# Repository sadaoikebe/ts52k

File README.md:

# TS52K — 無線版

親指シフト（NICOLA配列）を前提に設計した、52キーの自作キーボードです。このブランチは、MDBT50Q-1MV2 と ZMK で動かす無線版です。ケースとプレートは RP2040 版と共通です。

解説記事: [親指シフトキーボードを作った話](https://qiita.com/sadaoikebe/items/e3715383058286457a23)

## 特徴

- **親指シフト専用設計** — かな入力だけでなく、英数レイヤーも親指シフトで打てる配列
- **52キー + ロータリーエンコーダ** — 50%サイズに親指キーを確保したレイアウト
- **ZMK** — 有線のときは USB HID、ケーブルを抜くと BLE
- **MDBT50Q-1MV2** — Raytac の nRF52840 モジュール。チップアンテナ付き。技適あり
- **USB-C が一つ** — 有線キーボード、充電、あとからの UF2
- **保護付きの LiPo** — 過放電保護はセル側。基板側コネクタはJST PH横挿しSMT、電池製品は後で選ぶ
- **JLCPCB で発注できる基板** — モジュールは在庫 0 なので、事前発注してから PCBA
- **FDM 3Dプリンタで出力できるケース** — 特殊な設備なしで製作可能

---

## このブランチ

回路図は無線版へ更新しました。既存の配置を引き継いだ親シートと、MDBT50Q・電源容量・LF水晶の子シートの2枚です。[回路図PDF](pcb/schematic-review/ts52k-wireless.pdf)と[配置元・確認記録](notes/wireless-schematic-layout.md)を参照してください。PCBは2026-11-10にU5を西端へ移し、GPIO割当てと西側の配置・配線を更新しました。[配置画像・記録](pcb/placement-review/README.md)を参照してください。取り込み判断・実機検証・無線版の製造データ作成は未了です。

現行の決定は[無線版の決定事項](notes/wireless-decisions.md)に集約しています。BOMは20品種・82点で（2026-11-11に電池の逆接続保護Q1を追加）、回路図から参照番号付きで照合済みです。ERCはエラー・警告とも0件。電池・ケース、SWD機材の購入判断は後日です。

使用しているKiCad MCPとローカル開発環境は[KiCad開発環境の記録](pcb/DEVELOPMENT.md)を参照してください。

## リポジトリ構成

```
pcb/     KiCad 10 プロジェクト。回路図・PCBは無線版、U5西端移設後
         子シート pcb/mdbt50q.kicad_sch
         schematic-review/ — PDF、画像、ERC、参照番号付きBOMと検査結果
         placement-review/ — PCB配置・配線画像と各時点の照合結果
         PLACEMENT.md — RP2040 版の基板レイアウトガイド
case/    FreeCAD ソース、3Dプリント用 3MF、プレート加工用 DXF
```

`pcb/` は無線版で使うシンボルとフットプリントを同梱しています。回路図とPCBの旧部品・旧ライブラリ参照は除去済みです。

| ライブラリ | 内容 |
| :--- | :--- |
| `MX_Only.pretty` | Cherry MX キースイッチのフットプリント（1U〜3U、7種） |
| `ts52k.kicad_sym` / `.pretty` | 無線版の選定済み20品種とMXシンボル。採用ランド15種を同梱 |
| `tag-connect.kicad_sym` | Tag-Connect TC2030のSWDシンボル。既定ランドは`ts52k.pretty`に同梱 |

選定済み部品の登録、回路図への反映とPCBへの取り込みは完了しています。[ライブラリの出典・変更・削除内容](pcb/LIBRARIES.md)と[部品ごとのシンボル／ランド対応表](pcb/wireless-library.csv)を参照してください。全配線を接続した後の設計レビュー・実機検証は残っています。

---

## 回路の構成

```
USB-C (J1) ─┬─ VBUS ─┬─→ BQ24072 IN（1 µF）
            │        └─ 2.2 Ω ─→ モジュール VBUS（パッド 32、4.7 µF）
            └─ D−/D+ ──→ モジュール パッド 34 / 35
                         ESD は H5VU10U。データ線に直列抵抗は置かない

BQ24072 OUT（4.7 µF）──→ モジュール VDDH（パッド 30）
BQ24072 BAT（4.7 µF）──→ JST PH 2極（1=BAT+、2=GND）──→ 保護付きセル

モジュール VDD（パッド 28）──→ J2 の 1 番。電圧は REGOUT0 = 3.3 V
モジュール ── 16本 ──→ キーマトリクス（6列×10行）
          ── 2本   ──→ エンコーダの回転（A=P1.11、B=P1.13）
          ── SWD ──→ J2 の 2 番 SWDIO（パッド 51）、4 番 SWCLK（パッド 53）
SW1 ──→ P0.18（nRESET）を GND へ。電源を切らずに 500 ms 以内の 2 回押しで UF2
```

モジュールは MDBT50Q-1MV2 です。P1MV2 との差はアンテナだけで、技適は両方にあります。外形は 10.5 × 15.5 × 2.05 mm、供給は 1.7〜5.5 V です。アンテナは削ったり、足したりしません。32 MHz と無線側のインダクタはモジュールの中にあります。GPIO は 48 本が 61 パッドに出ています。

### USB

J1 は HRO TYPE-C-31-M-12 のままです。CC1 / CC2 は 5.1 kΩ で GND、シールドは GND、D− / D+ / VBUS の ESD は H5VU10U です。D+ / D− の直列抵抗は、nRF の USB PHY に入っているので置きません。

PC に挿すと、ZMK は既定で USB HID に出します。ケーブルを抜くと最後の BLE プロファイルに戻ります。切り替えは `&out` で、選択は残ります。充電器のように HID を受け取らない相手では `OUT_BLE` にします。キーマップだけの変更は ZMK Studio が USB でも BLE でもできます。

VBUS（パッド 32）は、モジュールの USB 用 3.3 V レギュレータへの 5 V 入力です。充電 IC の出力はここへ入れません。

モジュールVBUS枝には、Nordic推奨・Raytac参考回路の2.2 Ωを入れます。C22939（0603・Basic）を1個、4.7 µFは抵抗の後、VBUSのESDは手前です。BQ24072 INは抵抗の手前から分岐します。[選定根拠と接続](notes/wireless-power-input.md)を参照してください。

### 電源

セルの電圧を VDDH（パッド 30）へ入れ、モジュール内のレギュレータでコアを作ります。ZMK の nice!nano v2 は `zmk,battery-nrf-vddh` で、このピンを読みます。外の 3.3 V で VDD と VDDH を短絡する結線にはしません。この基板には灯が無く、他の基板へ 3.3 V を出すピンもありません。

GPIO の High は REGOUT0 です。nice!nano のブートローダに合わせて 3.3 V にします。UICR の生の数値は、ブートローダのソースからは写していません。未設定のままでは VDD が 1.8 V になります。

検証済みのZMK main最小構成に合わせ、REG0（高電圧側）・REG1（無線側）のDC/DCを両方オンにします。REG1のインダクタは内蔵、REG0用にはDCCH（31）–VDD（28）へ10 µHのLQM18DN100M70L / C713281を外付けします。P0.13のVCCスイッチは置かず、この端子はrow3に使います。VDDHに10 µF、VDDには4.7 µF＋1 µF＋100 nF×3を置きます。[現行BOMと根拠](notes/wireless-bom-candidates.md)を参照してください。

LFクロックは外付け32.768 kHz水晶、XTAL/50 ppm設定です。FC-12M / X1A0000610008（CL=9 pF）をXL1（17）–XL2（18）へ接続し、各端子からGNDへ12 pFを1個ずつ置きます。

### 充電

充電 IC は BQ24072 です。パッケージは VQFN-16（RGT、3.00 mm × 3.00 mm）、リール品の記号は BQ24072RGTR です。T 付きの BQ24072T は使いません。TS の見方が違い、10 kΩ 固定では充電しません。

nice!nano v2の公開回路図はBQ24075表記です。量産でBQ24072を使ったという発言は[調査記録](notes/wireless-bom-candidates.md)に出典と限界を残しています。今回の72の選定は、公開図と型番が同一という理由ではなく、VDDHへ供給するOUTの電圧条件に基づきます。SLUS810Nでは72のOUTはVBAT + 225 mV（VBATが3.2 V以上のとき+150 / +225 / +270 mV。3.2 V未満で入力があるときは3.3 / 3.4 / 3.5 V）です。4.2 Vのセルなら上側は約4.47 Vです。75のOUTは5.4 / 5.5 / 5.6 Vで、最大はモジュールの供給範囲1.7〜5.5 Vの上に出ます。

ピンは SLUS810N のピン図です。

| ピン | つなぎ |
| :--- | :--- |
| IN（13） | USB 5 V。1 µF。過電圧保護は typ 6.6 V（6.4〜6.8 V）。バイパスの範囲は 1〜10 µF |
| BAT（2、3） | 保護付きセルのプラス。充電電圧は 4.2 V。4.7 µF |
| OUT（10、11） | モジュール VDDH（パッド 30）。4.7 µF。範囲は 4.7〜47 µF。入力が無いときは BAT とつながる |
| EN1（6）、EN2（5） | 両方 GND。USB100 で入力上限は 100 mA（90 / 95 / 100 mA） |
| ISET（16） | 8.2 kΩ / C25981をGNDへ。Basic優先で選定。KISET = 890 AΩで約108.5 mAの設定だが、実際の充電電流はUSB100の入力制限とシステム負荷にも制限される |
| ILIM（12） | 1.5 kΩ を GND へ。データシートの試験条件。USB100 の電流を決めるのは EN の側。開放にはしない |
| TS（1） | 10 kΩ を GND へ。パックの NTC は引かない |
| TD（15） | GND。充電終止を有効にする。開放にはしない |
| CE（4） | GND。High で充電が止まり、OUT は生きたまま |
| TMR（14） | 開放。タイマは既定値 |
| CHG（9）、PGOOD（7） | 灯が無いので未接続 |
| VSS（8）とサーマルパッド | 両方 GND。パッドだけを GND にしない |

セルの容量はまだ決まっていないので、500 mA（EN1 = High、EN2 = Low）にはしません。nice!nano の公称も 100 mA です。BQ24072 に過放電保護は無く、短絡保護はあります。基板に保護 IC は足しません。セルを切り離す SYSOFF は 75 と 79 のピンで、72 にはありません。ロードスイッチは足しません。

コネクタはJST S2B-PH-SM4-TB(LF)(SN) / C295747で、基板側は1=BAT+、2=GNDに統一します。コネクタの1番とBQ24072のBATの間には、逆接続保護のPチャネルMOSFET（Q1、AO3401A / C15127）が直列に入っています。逆向きの電池をつないでもQ1がオフのままで、充電ICとモジュールに負電圧がかかりません。極性の確認が不要になるわけではありません（[手順書](notes/brick-avoidance.md)）。電池の容量・外形・製品は後で選び、ケーブルの実際の極性を基板に合わせます。PHシリーズ共通の極性規約を意味しません。

### キーの配線

52個のキーは、1個ずつマイコンのピンには繋ぎません。6列×10行のマトリクスです。列を1本ずつ順に駆動し、10本の行の電圧を見て、どのキーが押されているかを判断します。キーごとにダイオードが1本あり、向きはカソードが行側です。

エンコーダの押し込みスイッチも、このマトリクスの6列目に入っています。キー52と押し込み1つで、接点は53です。エンコーダの回転（A相とB相）はマトリクスの外で、専用のピンが2本です。

列と行でマイコンのピンは16本、回転と合わせて18本です。2026-11-10のU5西端移設に合わせ、上段バスの入力6本を北側パッド4・6・8・10・12・14、下段の行6本を南側パッド37・41・43・44・46・48へ割り当てました。列6本は制限なしのパッド16・20・22・24・26・49を使い、ZMKで高駆動を明示します。ダイオードは反転しません。[現在のGPIO表](notes/wireless-pin-assignment.md)は回路図・PCBへ反映済みで、ファームウェア側への反映は[ZMK同期チェックリスト](notes/zmk-pin-sync-checklist.md)に従って行います。

### 書き込み

通常のRaytacモジュールはAdafruit UF2ブートローダーなしを想定し、初回はJ2のSWDから書き込みます。検証対象はAdafruit 0.11.0のnice_nano用SoftDevice結合HEXです。秋月の書き込み済みモジュールも調達対案ですが、搭載版と電源初期化条件の照合が必要です。SWDランドはどちらでも必須、機材と購入先の決定は後日とします。[調査記録](notes/swd-equipment.md)を参照してください。

J2 は Tag-Connect TC2030 のランドだけです。部品は実装しません。初回書き込み・復旧の手順と、基板を壊さないための注意（電池の極性、3.3 V固定の書き込み器を使わない等）は[文鎮化回避の運用ルールと手順](notes/brick-avoidance.md)にまとめています。

| ピン | つなぎ |
| :--- | :--- |
| 1 | モジュール VDD（パッド 28） |
| 2 | SWDIO（パッド 51） |
| 3 | P0.18（nRESET）。SW1 と同じネット |
| 4 | SWCLK（パッド 53） |
| 5 | GND |
| 6 | SWO。未接続 |

SW1 は TS-1187A-B-A-B のまま、P0.18 を GND に落とすリセットにします。BOOTSEL 用の直列 1 kΩ は残しません。nRESET のプルアップは内蔵です。

---

## ロータリーエンコーダ

SW2 は型番未確定の EC11 互換です。押し込みは `col6` に入っています。A/B の 10 kΩ と 100 nF は外します。nRF52840 の内蔵プルアップは 11〜16 kΩ（別の回答は 13 kΩ）で、RP2040 の 50〜80 kΩ を前提にした回路は移しません。

---

## 部品リスト

回路図の実装対象BOMは**20品種・82点**です。[参照番号付きBOM](pcb/schematic-review/bom.csv)を回路図から生成し、[選定済みBOM](notes/wireless-bom-draft.csv)と一致することを確認しました。選定根拠は[先行例との対応](notes/wireless-bom-candidates.md)、実装条件は[ランド・配置の照合](notes/wireless-layout-check.md)にまとめています。実装座標はPCB移行後です。

### 残すもの、足すもの

| 部品 | 型番 / 値 | 数量 | パッケージ |
| :--- | :--- | ---: | :--- |
| モジュール | MDBT50Q-1MV2 / C5118826 | 1 | 10.5×15.5×2.05 mm |
| 充電 IC | BQ24072RGTR / C140288 | 1 | VQFN-16 3×3 mm |
| REG0 インダクタ | LQM18DN100M70L / C713281、10 µH | 1 | 0603 |
| LF 水晶 | X1A0000610008 / C96341、32.768 kHz | 1 | FC-12M、2012 |
| LF 負荷容量 | 12 pF / C1547 | 2 | 0402 |
| USB-C | HRO TYPE-C-31-M-12 / C165948 | 1 | SMD端子・スルーホール固定脚 |
| USB ESD | H5VU10U / C22395519 | 3 | DFN1006-2L |
| リセット | TS-1187A-B-A-B / C318884 | 1 | 上押し 5.1×5.1×1.5 mm |
| ダイオード | 1N4148W / C81598 | 53 | SOD-123 |
| CC 抵抗 | 5.1 kΩ / C23186 | 2 | 0603 |
| VBUS 直列抵抗 | 2.2 Ω / C22939（Basic） | 1 | 0603 |
| ISET | 8.2 kΩ / C25981 | 1 | 0603 |
| ILIM | 1.5 kΩ / C22843 | 1 | 0603 |
| TS | 10 kΩ / C25804 | 1 | 0603 |
| IN、VDD のコンデンサ | 1 µF / C15849 | 2 | 0603 |
| OUT、BAT、VBUS、VDD のコンデンサ | 4.7 µF / C19666 | 4 | 0603 |
| VDD のバイパス容量 | 100 nF / C14663 | 3 | 0603 |
| VDDH のコンデンサ | 10 µF / C15850 | 1 | 0805 |
| 電池コネクタ | S2B-PH-SM4-TB(LF)(SN) / C295747 | 1 | PH横挿しSMT、2極 |

Tag-ConnectのJ2はランドだけです。電源コンデンサの構成と選定根拠は[選定記録](notes/capacitor-selection.md)を使います。

### 手付け・機構部品

| 部品 | ソース | 数量 | 備考 |
| :--- | :--- | ---: | :--- |
| キースイッチ | AliEx / 淘宝 / 自キ専門店 | 52 | お好みの打鍵感で。Kailh Box 白軸がおすすめ |
| ロータリーエンコーダ | — | 1 | Alps EC11E 互換、押し込みスイッチ付き。型番未定 |
| 2u スタビライザー | AliEx / 淘宝 / 自キ専門店 | 3 | PCBマウント |
| 3u スタビライザー | AliEx / 淘宝 / 自キ専門店 | 1 | PCBマウント |
| キーキャップ | AliEx / 淘宝 / 自キ専門店 | 1セット | **3u と 2.75u の親指キーが必要** |
| ケース ふた | [3Dプリント](case/) | 1 | FDM で出力可能 |
| ケース 底板 | [3Dプリント](case/) | 1 | FDM で出力可能 |
| 定位板（プレート） | [レーザーカット](case/) | 1 | t=1.5 mm 真鍮 |
| セル | — | 1 | 保護付き LiPo。容量と外形はケースのとき |
| ヒートセットインサート | [AliExpress](https://www.aliexpress.com/item/1005002288716120.html) | 8 | M3 × 6 mm × 4.6 mm。長さは 6 mm でなくても可 |
| M3 円頭六角ボルト | — | 8 | 6 mm |
| クッション | — | 12 | Poron / EVA フォーム、2 mm 厚 × 2 mm × 87 mm |
| ゴム足 | — | 4〜 | — |

キースイッチの内訳: 1U ×39、1.25U ×5、1.5U ×2、1.75U ×2、2.25U ×2、2.75U ×1、3U ×1

### まだ決めていない

- **実際の部品配置** — U5を基板西端に移設し、モジュールの全層アンテナ禁止領域と、基板端に沿って拡張した `ANT_EDGE` を設定済みです。[配置記録](pcb/placement-review/README.md)を参照してください。実機の通信距離は未確認です。
- **SWD機材・モジュールの購入先** — 調査記録を残し、決定は後日。
- **電池製品** — 容量と外形は後で選びます。今回ケースの設計は行いません。
- **エンコーダ SW2** — 型番。RP2040 版から未定のままです。

---

## 回路図に反映した変更

### 維持したもの

- キー、1N4148W が 53 個、6列×10行。回路図のネット名は `col1`〜`col6`、`row1`〜`row10`。ダイオードのカソードは行側。エンコーダの押し込みは6列目。エンコーダ本体 SW2。
- J1。R5 と R6（5.1 kΩ）。シールドは GND。D89、D90、D91（H5VU10U）。
- J2 のランド。上のピン表。
- SW1 の部品。つなぎ先は P0.18。

### 除去したもの

旧RP2040子シートごと除去しました。

- U5 RP2040
- X2。12 MHz の OC2EL89CJO-113YLC-12M
- R3、R4。RUN と発振器 EN の 10 kΩ
- R7、R8。USB の直列 22 Ω
- R9〜R13。QSPI の直列 22 Ω
- C6〜C10、C12〜C18、C21。1 µF

親シートから除去しました。

- U4 W25Q128。R2（CS の 10 kΩ）
- R14（1 kΩ）。SW1 には残しません
- U3 TPS7A2433。C3（4.7 µF、0603）、C5（4.7 µF、0402）
- C2、C4。その 3.3 V の 1 µF
- R15、R16（エンコーダの 10 kΩ）、C19、C20（100 nF）

### 追加したもの

- MDBT50Q-1MV2 と GND。6列×10行の16本と、エンコーダの回転2本は[GPIO接続表](notes/wireless-pin-assignment.md)の割当てを使う
- VDD（パッド28）–GNDに4.7 µF＋1 µF＋100 nF×3。[電源コンデンサの現行選定](notes/capacitor-selection.md)を使う
- DCCH（31）–VDD（28）へ10 µH、VDDH（30）–GNDへ10 µF
- XL1（17）–XL2（18）へFC-12M、各端子からGNDへ12 pFを1個ずつ
- BQ24072 と、上のピン表の抵抗・コンデンサ
- OUTをVDDH（30）へ。USB 5 Vは別枝の2.2 Ωを介してVBUS（32）へ、4.7 µFは抵抗の後
- D− をパッド 34、D+ をパッド 35 へ
- 電池コネクタS2B-PH-SM4-TB(LF)(SN)。1=BAT+、2=GND
- アンテナの全層禁止領域と局所的な実装面禁止領域を登録ランドへ含めた。PCBでの拡張・配置は[寸法と配置条件](notes/wireless-layout-check.md)に従う

### 採用しないもの

- NFC
- 外の 3.3 V で VDD と VDDH を短絡する結線
- P0.13 のロードスイッチ
- LED、USBデータ線の直列抵抗、エンコーダのRC
- ドングル用ブートローダの P0.15 と P0.10
- 基板上の電池保護IC、電池プラス側のスイッチ、DW01AとFS8205。電池保護はパック側

---

## 配置と製造

モジュールは B.Cu、真鍮の定位板 t=1.5 mm は F 面、電波は樹脂の底板側へ抜けます。承認書 2.3 は、アンテナの位置を全層で GND 無し、できるだけ広く、端の方が中央より良い、と書いています。エンコーダの金属筐体はアンテナの近くに置きません。モジュールの高さは 2.05 mm です。

MDBT50Q-1MV2 の JLCPCB 部品番号は C5118826 です。2026-10-31 の表示は在庫 0、Standard Only、X-ray 必須でした。在庫が無くても Parts Manager で事前発注し、私有庫に入ってから PCBA に出します。生基板の最少は 5 枚です。Standard はエッジレールが要り、レール幅のヘルプは最小 5 mm です。レールは製品の外形に残しません。自宅リフローは、事前発注が通らないときの予備です。

Fanstel BC840 は使いません。同じ机の上でも、MDBT50Q より距離の余裕が小さく、縁ゼロのアンテナ条件は残ります。

---

## ファームウェア

無線版はZMKです。開発は別リポジトリ`C:\Users\marur\zmk-config`で行い、本リポジトリはハードウェアを扱います。ZMK main `4dd95d7840eb3d5a3f59bb29fbf1ab054715ef85` / Zephyr 4.1.0で、TS52Kの1×1最小定義をビルド済みです。VDDH給電、REG0/REG1 DC/DCともオン、外付けLF水晶XTAL/50 ppm、USB/BLE、P0.18リセット。P0.13の`EXT_POWER`は使いません。GPIO18本の全マトリクスと親指シフトの実装は今後のファームウェア開発で行います。

ビルド成功は実機の起動確認ではありません。初回SWD、USBブートローダー、最小ZMK、BLEの順に試作基板で確認します。[起動条件の調査記録](notes/zmk-hardware-bringup.md)を参照してください。

有線版の QMK は別リポジトリです。公開済みの `ts52k` 定義は ATmega32U4 用です。

https://github.com/sadaoikebe/qmk_firmware/tree/master/keyboards/ts52k

---

## 組み立て手順

ケース、プレート、キースイッチの手順はRP2040版と同じです。電池の入れ方は電池製品を選んだ後で書きます。SW1はBOOTSELではなくリセットです。ケースの穴は、このボタンを押すためのものです。

### 1. 部品の確認

部品リストの通り揃っているか確認します。

### 2. スタビライザーの取り付け

**ここが一番の要注意ポイントです。** ちゃんと嵌っていないと、後の工程で気づいたときに大幅な手戻りになります。基板にスタビライザーを取り付けたら、爪がしっかりロックされているか1つずつ確認してください。

### 3. ロータリーエンコーダの取り付け

### 4. プレートとキースイッチの取り付け

プレートを貫通させて、**まず四隅のキースイッチから固定**します。四隅が決まるとプレートと基板の位置が安定するので、残りが入れやすくなります。

### 5. Poron フォームの貼り付け

### 6. ケースへのヒートセットインサート挿入

半田ごてで温めながら、**まっすぐ**押し込みます。斜めに入ると取り返しがつかないので、少しずつ確認しながら進めてください。

### 7. ケースの組み立て

---

## 開発環境

- **KiCad 10.0** 以降

無線版回路図のERCはエラー0・警告0です。[検査スクリプト](pcb/check_schematic.py)で電源・信号・BOM・旧マトリクスとの一致を確認し、[結果](pcb/schematic-review/validation.json)を保存しました。ライブラリ検査は[別記録](pcb/LIBRARIES.md)です。PCBは旧版なので、無線版DRC・schematic parityの検査はこれからです。RP2040版の0件という過去結果を現在のPCB整合の結果として使いません。

**`Tools → Update PCB from Schematic` では `Link footprints using reference designators` をオフのままにしてください。** フットプリントは Unique ID で回路図と紐付いています。

基板を編集する場合は、[`pcb/PLACEMENT.md`](pcb/PLACEMENT.md) の「やってはいけないこと」を先に読んでください。`PLACEMENT.md` が説明しているのは RP2040 版の配置です。編集後はベタを再充填し、DRC と製造データを作り直します。

```sh
kicad-cli sch erc                                   -o erc.rpt ts52k.kicad_sch
kicad-cli pcb drc --schematic-parity --refill-zones -o drc.rpt ts52k.kicad_pcb
```

---

## ライセンス

[Creative Commons Attribution-NonCommercial 4.0 International (CC BY-NC 4.0)](LICENSE.md)

複製・改変・再配布が可能です。ただし以下の条件が付きます。

- **表示（Attribution）** — 作者のクレジット表示、ライセンスへのリンク、変更の有無の明示が必要です
- **非営利（NonCommercial）** — 商用目的での利用はできません

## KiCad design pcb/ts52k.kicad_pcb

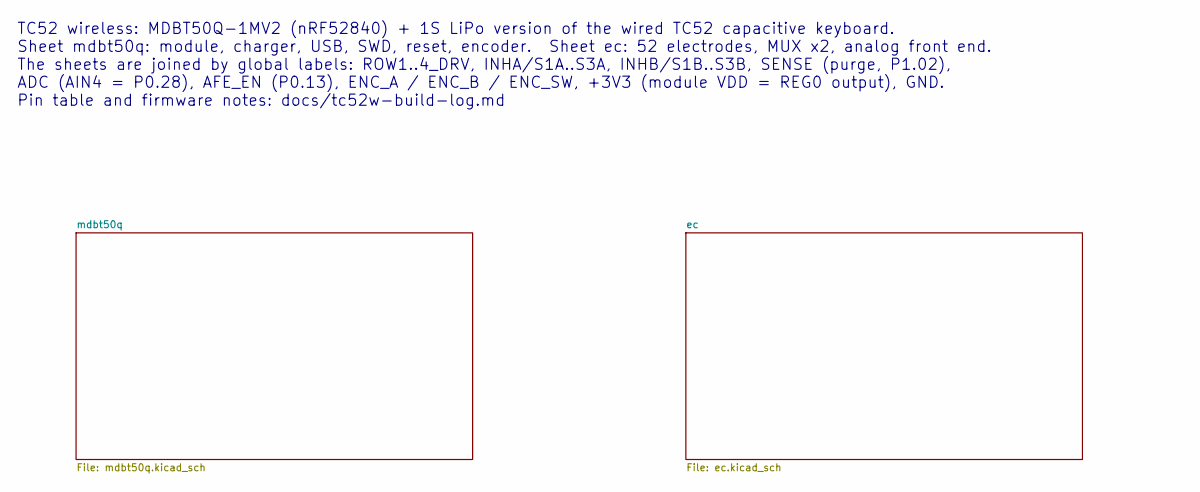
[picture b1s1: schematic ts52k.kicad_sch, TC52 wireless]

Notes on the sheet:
TC52 wireless: MDBT50Q-1MV2 (nRF52840) + 1S LiPo version of the wired TC52 capacitive keyboard. Sheet mdbt50q: module, charger, USB, SWD, reset, encoder. Sheet ec: 52 electrodes, MUX x2, analog front end. The sheets are joined by global labels: ROW1..4_DRV, INHA/S1A..S3A, INHB/S1B..S3B, SENSE (purg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

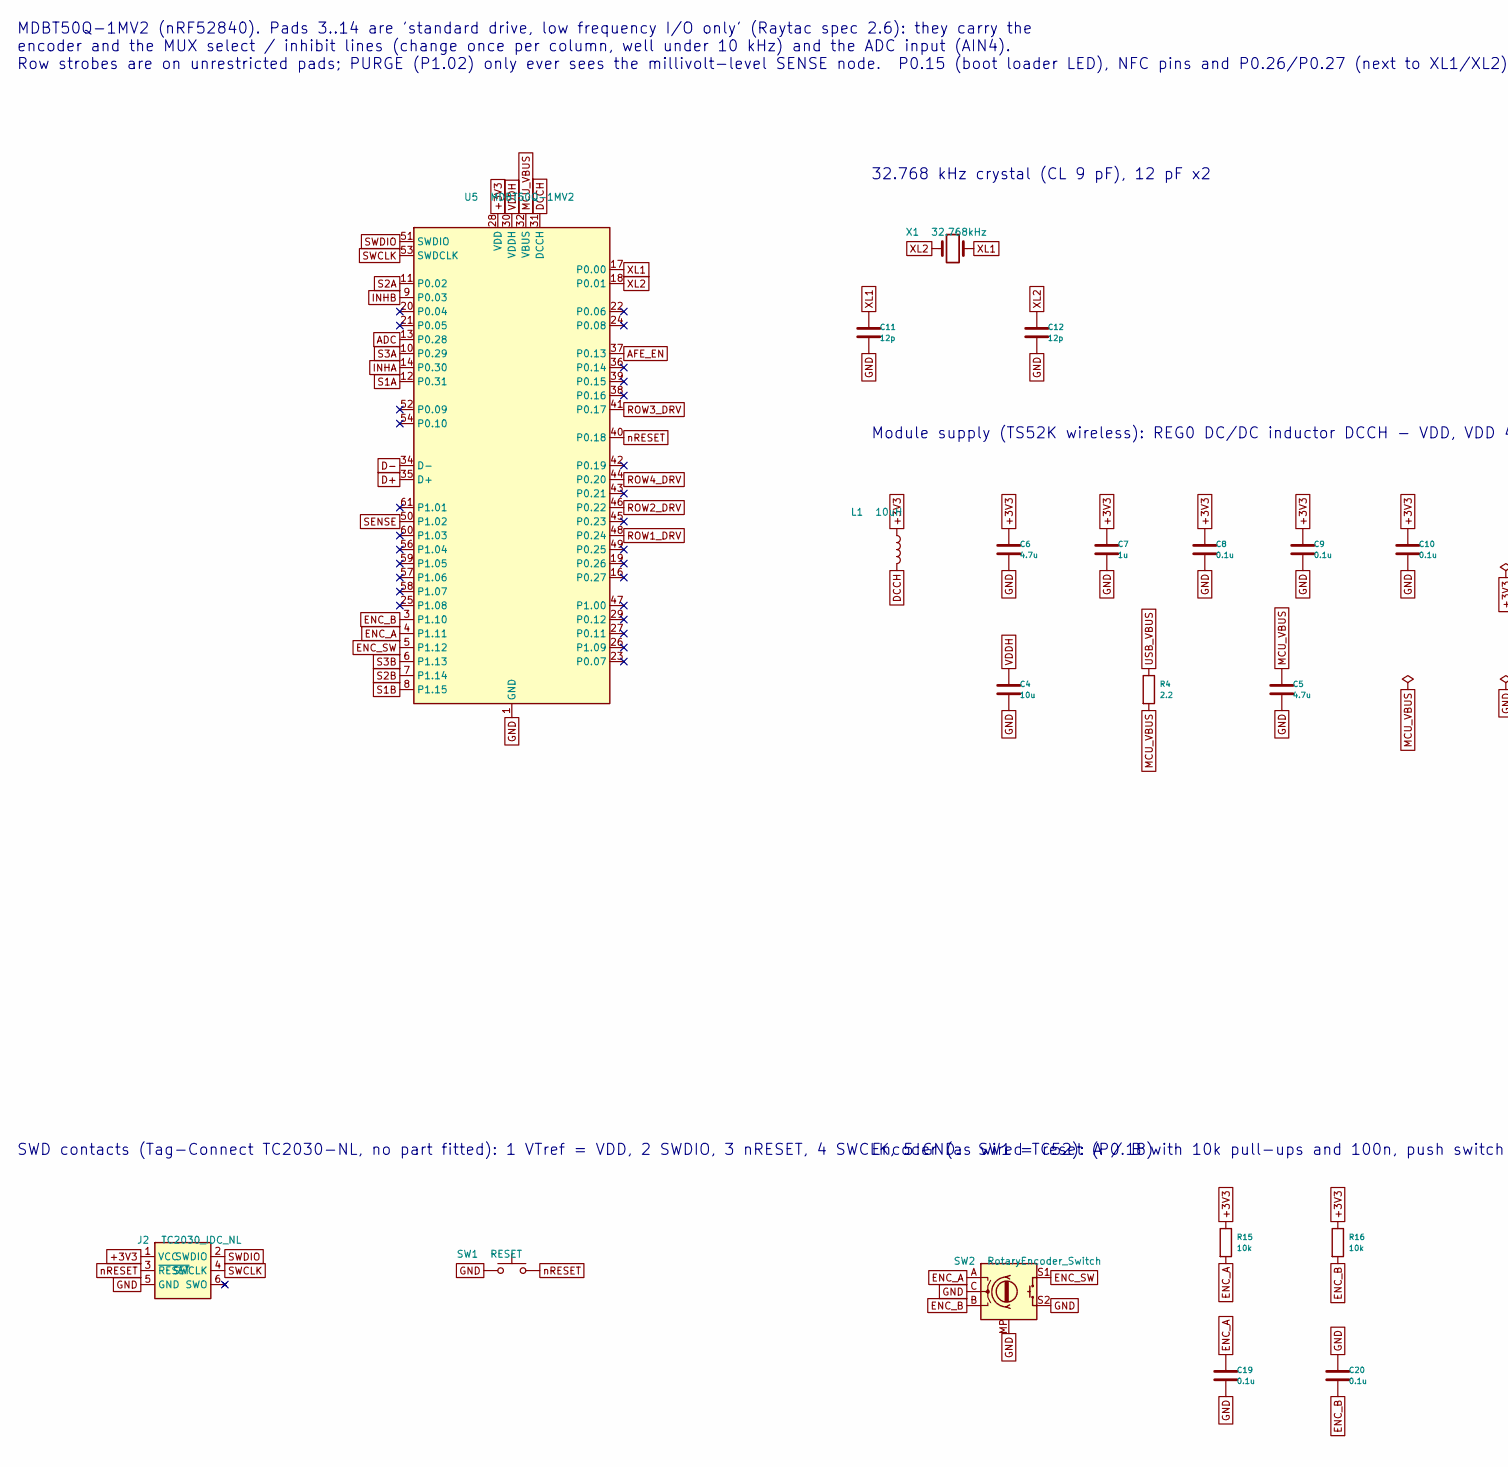
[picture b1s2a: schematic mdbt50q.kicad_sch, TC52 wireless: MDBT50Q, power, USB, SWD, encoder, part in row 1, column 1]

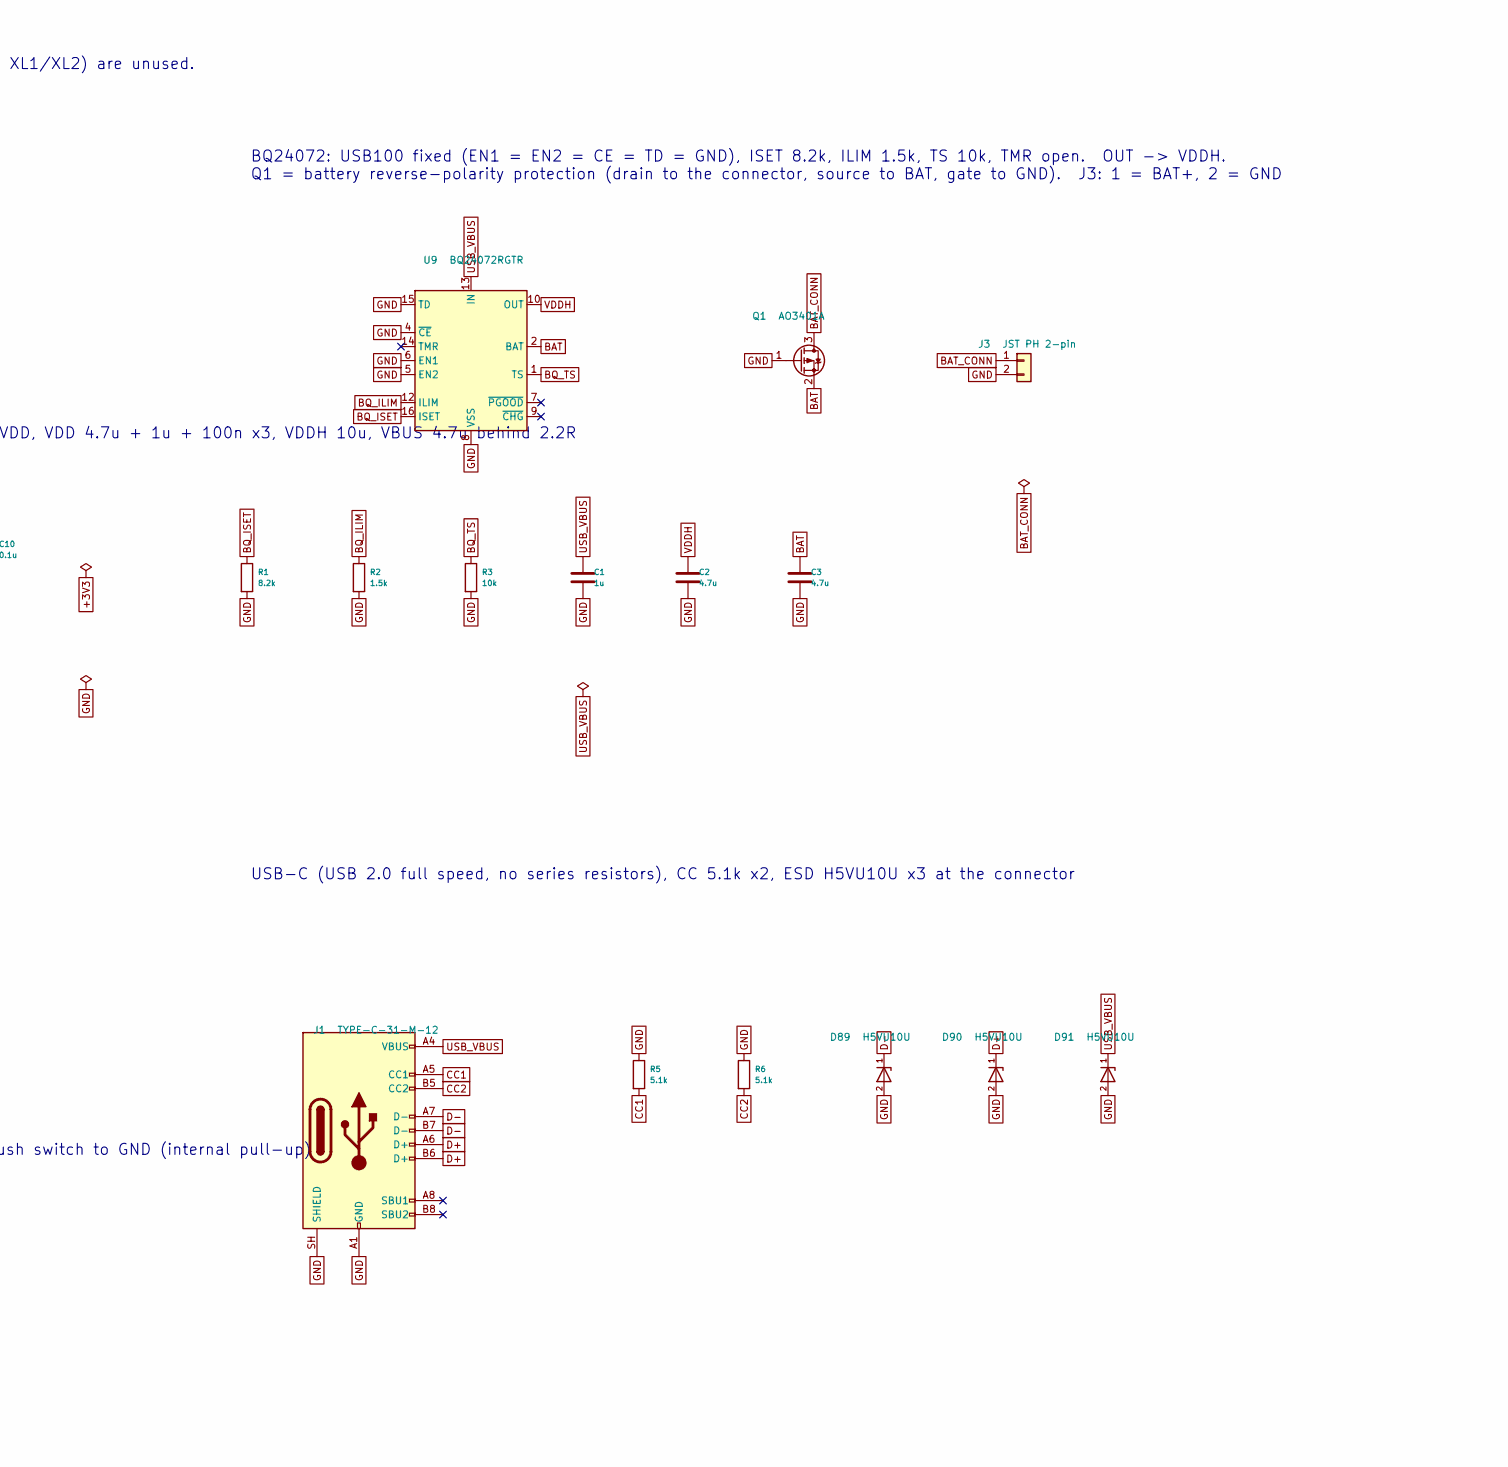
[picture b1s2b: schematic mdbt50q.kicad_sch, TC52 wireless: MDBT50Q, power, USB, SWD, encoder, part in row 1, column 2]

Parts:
C1, C7: 1u; C_0603_1608Metric; MPN CL10A105KB8NNNC; LCSC C15849
C2, C3, C5, C6: 4.7u; C_0603_1608Metric; MPN CL10A475KO8NNNC; LCSC C19666
C4: 10u; C_0805_2012Metric; MPN CL21A106KAYNNNE; LCSC C15850
C8, C9, C10, C19, C20: 0.1u; C_0402_1005Metric; MPN CL05B104KO5NNNC; LCSC C1525
C11, C12: 12p; C_0402_1005Metric; MPN 0402CG120J500NT; LCSC C1547
D89, D90, D91: H5VU10U; D_SOD-882D; MPN H5VU10U; LCSC C22395519
J1: TYPE-C-31-M-12; USB_C_Receptacle_HRO_TYPE-C-31-M-12; MPN TYPE-C-31-M-12; LCSC C165948
J2: TC2030_IDC_NL; Tag-Connect_TC2030-IDC-NL_2x03_P1.27mm_Vertical
J3: JST PH 2-pin; JST_PH_S2B-PH-SM4-TB_1x02-1MP_P2.00mm_Horizontal; MPN S2B-PH-SM4-TB(LF)(SN); LCSC C295747
L1: 10uH; L_0603_1608Metric; MPN LQM18DN100M70L; LCSC C713281
Q1: AO3401A; SOT-23; MPN AO3401A; LCSC C15127
R1: 8.2k; R_0603_1608Metric; MPN 0603WAF8201T5E; LCSC C25981
R2: 1.5k; R_0603_1608Metric; MPN 0603WAF1501T5E; LCSC C22843
R3: 10k; R_0603_1608Metric; MPN 0603WAF1002T5E; LCSC C25804
R4: 2.2; R_0603_1608Metric; MPN 0603WAF220KT5E; LCSC C22939
R5, R6: 5.1k; R_0603_1608Metric; MPN 0603WAF5101T5E; LCSC C23186
R15, R16: 10k; R_0402_1005Metric; MPN 0402WGF1002TCE; LCSC C25744
SW1: RESET; SW_Tactile_XKB_TS-1187A_5.1x5.1mm; MPN TS-1187A-B-A-B; LCSC C318884
SW2: RotaryEncoder_Switch; RotaryEncoder_Alps_EC11E-Switch_Vertical_H20mm
U5: MDBT50Q-1MV2; Raytac_MDBT50Q; MPN MDBT50Q-1MV2; LCSC C5118826
U9: BQ24072RGTR; VQFN-16-1EP_3x3mm_P0.5mm_EP1.68x1.68mm; MPN BQ24072RGTR; LCSC C140288
X1: 32.768kHz; Crystal_Epson_FC-12M_2.05x1.2mm; MPN X1A0000610008; LCSC C96341

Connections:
+3V3: C6.1, C7.1, C8.1, C9.1, C10.1, J2.1 (VCC), L1.1, R15.1, R16.1, U5.28 (VDD); also elsewhere on the board
ADC: U5.13 (P0.28); also elsewhere on the board
AFE_EN: U5.37 (P0.13); also elsewhere on the board
BAT: C3.1, Q1.2 (S), U9.2 (BAT), U9.3 (BAT)
BAT_CONN: J3.1, Q1.3 (D)
BQ_ILIM: R2.1, U9.12 (ILIM)
BQ_ISET: R1.1, U9.16 (ISET)
BQ_TS: R3.1, U9.1 (TS)
CC1: J1.A5 (CC1), R5.2
CC2: J1.B5 (CC2), R6.2
D+: D90.1 (IO), J1.A6 (D+), J1.B6 (D+), U5.35 (D+)
D-: D89.1 (IO), J1.A7 (D-), J1.B7 (D-), U5.34 (D-)
DCCH: L1.2, U5.31 (DCCH)
ENC_A: C19.1, R15.2, SW2.A, U5.4 (P1.11)
ENC_B: C20.2, R16.2, SW2.B, U5.3 (P1.10)
ENC_SW: SW2.S1, U5.5 (P1.12)
GND: C1.2, C2.2, C3.2, C4.2, C5.2, C6.2, C7.2, C8.2, C9.2, C10.2, C11.2, C12.2, C19.2, C20.1, D89.2 (GND), D90.2 (GND), D91.2 (GND), J1.A1 (GND), J1.A12 (GND), J1.B1 (GND), J1.B12 (GND), J1.SH (SHIELD), J2.5 (GND), J3.2, Q1.1 (G), R1.2, R2.2, R3.2, R5.1, R6.1, SW1.1, SW2.C, SW2.MP, SW2.S2, U5.1 (GND), U5.2 (GND), U5.15 (GND), U5.33 (GND), U5.55 (GND), U9.4 (~CE), U9.5 (EN2), U9.6 (EN1), U9.8 (VSS), U9.15 (TD), U9.17 (VSS); also elsewhere on the board
INHA: U5.14 (P0.30); also elsewhere on the board
INHB: U5.9 (P0.03); also elsewhere on the board
MCU_VBUS: C5.1, R4.2, U5.32 (VBUS)
ROW1_DRV: U5.48 (P0.24); also elsewhere on the board
ROW2_DRV: U5.46 (P0.22); also elsewhere on the board
ROW3_DRV: U5.41 (P0.17); also elsewhere on the board
ROW4_DRV: U5.44 (P0.20); also elsewhere on the board
S1A: U5.12 (P0.31); also elsewhere on the board
S1B: U5.8 (P1.15); also elsewhere on the board
S2A: U5.11 (P0.02); also elsewhere on the board
S2B: U5.7 (P1.14); also elsewhere on the board
S3A: U5.10 (P0.29); also elsewhere on the board
S3B: U5.6 (P1.13); also elsewhere on the board
SENSE: U5.50 (P1.02); also elsewhere on the board
SWCLK: J2.4 (SWCLK), U5.53 (SWDCLK)
SWDIO: J2.2 (SWDIO), U5.51 (SWDIO)
USB_VBUS: C1.1, D91.1 (IO), J1.A4 (VBUS), J1.A9 (VBUS), J1.B4 (VBUS), J1.B9 (VBUS), R4.1, U9.13 (IN)
VDDH: C2.1, C4.1, U5.30 (VDDH), U9.10 (OUT), U9.11 (OUT)
XL1: C11.1, U5.17 (P0.00), X1.2
XL2: C12.1, U5.18 (P0.01), X1.1
nRESET: J2.3 (~RESET), SW1.2, U5.40 (P0.18)

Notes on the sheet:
MDBT50Q-1MV2 (nRF52840). Pads 3..14 are 'standard drive, low frequency I/O only' (Raytac spec 2.6): they carry the encoder and the MUX select / inhibit lines (change once per column, well under 10 kHz) and the ADC input (AIN4). Row strobes are on unrestricted pads; PURGE (P1.02) only ever sees the 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
32.768 kHz crystal (CL 9 pF), 12 pF x2
Module supply (TS52K wireless): REG0 DC/DC inductor DCCH - VDD, VDD 4.7u + 1u + 100n x3, VDDH 10u, VBUS 4.7u behind 2.2R
BQ24072: USB100 fixed (EN1 = EN2 = CE = TD = GND), ISET 8.2k, ILIM 1.5k, TS 10k, TMR open. OUT -> VDDH. Q1 = battery reverse-polarity protection (drain to the connector, source to BAT, gate to GND). J3: 1 = BAT+, 2 = GND
USB-C (USB 2.0 full speed, no series resistors), CC 5.1k x2, ESD H5VU10U x3 at the connector
SWD contacts (Tag-Connect TC2030-NL, no part fitted): 1 VTref = VDD, 2 SWDIO, 3 nRESET, 4 SWCLK, 5 GND. SW1 = reset (P0.18)
Encoder (as wired TC52): A / B with 10k pull-ups and 100n, push switch to GND (internal pull-up)

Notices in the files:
pcb/ts52k.kicad_pcb:
(C) 2023 Ikebe Sadao https://github.com/sadaoikebe
